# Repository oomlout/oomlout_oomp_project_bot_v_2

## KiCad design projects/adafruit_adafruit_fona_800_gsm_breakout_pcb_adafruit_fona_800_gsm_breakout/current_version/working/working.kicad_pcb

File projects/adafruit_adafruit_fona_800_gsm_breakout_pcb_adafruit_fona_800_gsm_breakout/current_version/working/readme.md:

# adafruit_fona_800_gsm_breakout_pcb
 
## summary 
* id: adafruit_adafruit_fona_800_gsm_breakout_pcb_adafruit_fona_800_gsm_breakout
* user: adafruit
* name: adafruit_fona_800_gsm_breakout_pcb
* board: adafruit_fona_800_gsm_breakout
* repo: https://github.com/adafruit/Adafruit-FONA-800-GSM-Breakout-PCB

* src_file_repo_sch: 
* src_file_repo_sch_link: https://github.com/adafruit/Adafruit-FONA-800-GSM-Breakout-PCB/tree/master/
* full details link: https://github.com/oomlout/oomlout_oomp_project_bot_v_2/tree/main/projects/adafruit_adafruit_fona_800_gsm_breakout_pcb_adafruit_fona_800_gsm_breakout/current_version/working  

## schematic  
  
[schematic (pdf)](working_schematic.pdf) 

## pcb  

[board (pdf)](working.pdf)  

## working_bom
| Id | Designator | Footprint | Quantity | Designation | Supplier and ref |  | None | 
| --- | --- | --- | --- | --- | --- | --- | --- | 
| 1 | U$34,U$33 | MOUNTINGHOLE_2.5_PLATED | 2 | MOUNTINGHOLE2.5 |  |  | [''] | 
| 2 | C1 | 0805-NO | 1 | 10ÂµF |  |  | [''] | 
| 3 | C17,C15 | RESPACK_4X0603 | 2 | 10pF |  |  | [''] | 
| 4 | D5,D6,D4,D3 | SOD-323 | 4 | 1N4148 |  |  | [''] | 
| 5 | CHRG0 | CHIPLED_0805_NOOUTLINE | 1 | ORANGE |  |  | [''] | 
| 6 | VBUS0,PWM0,ADC0 | 1X01-CLEANBIG | 3 |  |  |  | [''] | 
| 7 | PWRSTAT0,DONE0 | CHIPLED_0805_NOOUTLINE | 2 | GREEN |  |  | [''] | 
| 8 | D1 | SOD-123 | 1 | MMSZ5231BT1G |  |  | [''] | 
| 9 | R4,R2,R5 | 0805-NO | 3 | 1K |  |  | [''] | 
| 10 | SW1 | BTN_KMR2_4.6X2.8 | 1 | KMR2 |  |  | [''] | 
| 11 | C4,C6,C2 | 0805-NO | 3 | 33pF |  |  | [''] | 
| 12 | C9,C11 | 0805-NO | 2 | 10uF |  |  | [''] | 
| 13 | C3,C5,C10 | 0805-NO | 3 | 10pF |  |  | [''] | 
| 14 | FID1,FID3,FID2,FID5,FID4 | FIDUCIAL_1MM | 5 | FIDUCIAL" |  |  | [''] | 
| 15 | U1 | SIM800L | 1 | SIM800H/L |  |  | [''] | 
| 16 | R3 | 0805-NO | 1 | 2K |  |  | [''] | 
| 17 | C7 | C1210 | 1 | 100uF |  |  | [''] | 
| 18 | U2 | SOT23-5 | 1 | MCP73831T-2ACI/OT |  |  | [''] | 
| 19 | CN2 | JSTPH2 | 1 | JSTPH |  |  | [''] | 
| 20 | R1 | 0805-NO | 1 | 470 |  |  | [''] | 
| 21 | X4 | 4UCONN_18510 | 1 |  |  |  | [''] | 
| 22 | C14,C16 | RESPACK_4X0603 | 2 | 33pF |  |  | [''] | 
| 23 | Q1 | SC59-BEC | 1 | DTC143ZUAT106 |  |  | [''] | 
| 24 | U$10,U$36 | ADAFRUIT_5MM | 2 |  |  |  | [''] | 
| 25 | JP1 | 1X12-CB | 1 |  |  |  | [''] | 
| 26 | D2 | SOT363 | 1 | SMF05C |  |  | [''] | 
| 27 | TP1 | TP11R | 1 | TPTP11R |  |  | [''] | 
| 28 | X2 | 4UCONN_20329 | 1 | MicroB |  |  | [''] | 
| 29 | JP2 | 1X02_ROUND | 1 | MIC |  |  | [''] | 
| 30 | NETSTAT0 | CHIPLED_0805_NOOUTLINE | 1 | BLUE |  |  | [''] | 
| 31 | IC1 | TSSOP14 | 1 | 74VHCT125PW |  |  | [''] | 
| 32 | X1 | SMA_EDGELAUNCH_UFL | 1 |  |  |  | [''] | 
| 33 | JP3 | 1X02_ROUND | 1 | BUZZ |  |  | [''] | 
| 34 | U$26 | FONA_LOGO | 1 |  |  |  | [''] | 
| 35 | X6 | C707_10M006_512_2 | 1 | SIM_LOCKAMPHENOL |  |  | [''] | 

## bom_schematic
| Ref | Qnty | Value | Cmp name | Footprint | Description | Vendor | DNP | 
| --- | --- | --- | --- | --- | --- | --- | --- | 
| ADC0 | 1 | PINHD-1X1CB | PINHD-1X1CB | working:1X01-CLEANBIG |  |  |  | 
| C1 | 1 | 10ÂµF | CAP_CERAMIC0805-NOOUTLINE | working:0805-NO |  |  |  | 
| C2, C4, C6 | 3 | 33pF | CAP_CERAMIC0805-NOOUTLINE | working:0805-NO |  |  |  | 
| C3, C5, C10 | 3 | 10pF | CAP_CERAMIC0805-NOOUTLINE | working:0805-NO |  |  |  | 
| C7 | 1 | 100uF | C-USC1210 | working:C1210 |  |  |  | 
| C9, C11 | 2 | 10uF | CAP_CERAMIC0805-NOOUTLINE | working:0805-NO |  |  |  | 
| C14, C16 | 2 | 33pF | CAP_4PACK1206 | working:RESPACK_4X0603 |  |  |  | 
| C15, C17 | 2 | 10pF | CAP_4PACK1206 | working:RESPACK_4X0603 |  |  |  | 
| CHRG0 | 1 | ORANGE | LED0805_NOOUTLINE | working:CHIPLED_0805_NOOUTLINE |  |  |  | 
| CN2 | 1 | JSTPH | JST_2PIN | working:JSTPH2 |  |  |  | 
| D1 | 1 | MMSZ5231BT1G | DIODE-ZENERSOD123 | working:SOD-123 |  |  |  | 
| D2 | 1 | SMF05C | TVSARRAY_5LANE | working:SOT363 |  |  |  | 
| D3, D4, D5, D6 | 4 | 1N4148 | DIODESOD-323 | working:SOD-323 |  |  |  | 
| DONE0 | 1 | GREEN | LED0805_NOOUTLINE | working:CHIPLED_0805_NOOUTLINE |  |  |  | 
| FID1, FID2, FID3, FID4, FID5 | 5 | FIDUCIAL"" | FIDUCIAL{dblquote}{dblquote} | working:FIDUCIAL_1MM |  |  |  | 
| IC1 | 1 | 74125PW | 74125PW | working:TSSOP14 |  |  |  | 
| JP1 | 1 | PINHD-1X12-CB | PINHD-1X12-CB | working:1X12-CB |  |  |  | 
| JP2 | 1 | MIC | HEADER-1X2ROUND | working:1X02_ROUND |  |  |  | 
| JP3 | 1 | BUZZ | HEADER-1X2ROUND | working:1X02_ROUND |  |  |  | 
| NETSTAT0 | 1 | BLUE | LED0805_NOOUTLINE | working:CHIPLED_0805_NOOUTLINE |  |  |  | 
| PWM0 | 1 | PINHD-1X1CB | PINHD-1X1CB | working:1X01-CLEANBIG |  |  |  | 
| PWRSTAT0 | 1 | GREEN | LED0805_NOOUTLINE | working:CHIPLED_0805_NOOUTLINE |  |  |  | 
| Q1 | 1 | DTC143ZUAT106 | -NPN_DRIVER-SC59-BEC | working:SC59-BEC |  |  |  | 
| R1 | 1 | 470 | RESISTOR0805_NOOUTLINE | working:0805-NO |  |  |  | 
| R2, R4, R5 | 3 | 1K | RESISTOR0805_NOOUTLINE | working:0805-NO |  |  |  | 
| R3 | 1 | 2K | RESISTOR0805_NOOUTLINE | working:0805-NO |  |  |  | 
| SW1 | 1 | KMR2 | SWITCH_TACT_SMT4.6X2.8 | working:BTN_KMR2_4.6X2.8 |  |  |  | 
| TP1 | 1 | TPTP11R | TPTP11R | working:TP11R |  |  |  | 
| U1 | 1 | SIM800H/L | GSM_SIM800L | working:SIM800L |  |  |  | 
| U2 | 1 | MCP73831T-2ACI/OT | MCP73831/2 | working:SOT23-5 |  |  |  | 
| U$33, U$34 | 2 | MOUNTINGHOLE2.5 | MOUNTINGHOLE2.5 | working:MOUNTINGHOLE_2.5_PLATED |  |  |  | 
| VBUS0 | 1 | PINHD-1X1CB | PINHD-1X1CB | working:1X01-CLEANBIG |  |  |  | 
| X1 | 1 | SMACONNECTOR_EDGE_UFL | SMACONNECTOR_EDGE_UFL | working:SMA_EDGELAUNCH_UFL |  |  |  | 
| X2 | 1 | MicroB | USBMICRO_20329 | working:4UCONN_20329 |  |  |  | 
| X4 | 1 | AUDIO_3.5MMJACK_4POL | AUDIO_3.5MMJACK_4POL | working:4UCONN_18510 |  |  |  | 
| X6 | 1 | SIM_LOCKAMPHENOL | SIM_LOCKAMPHENOL | working:C707_10M006_512_2 |  |  |  | 

## mounting_holes
| x | y | package | value | ref | size | 
| --- | --- | --- | --- | --- | --- | 
| 26.67 | 0.0 | MOUNTINGHOLE_2.5_PLATED | MOUNTINGHOLE2.5 | U$33 | m3 | 
| 0.0 | 0.0 | MOUNTINGHOLE_2.5_PLATED | MOUNTINGHOLE2.5 | U$34 | m3 |

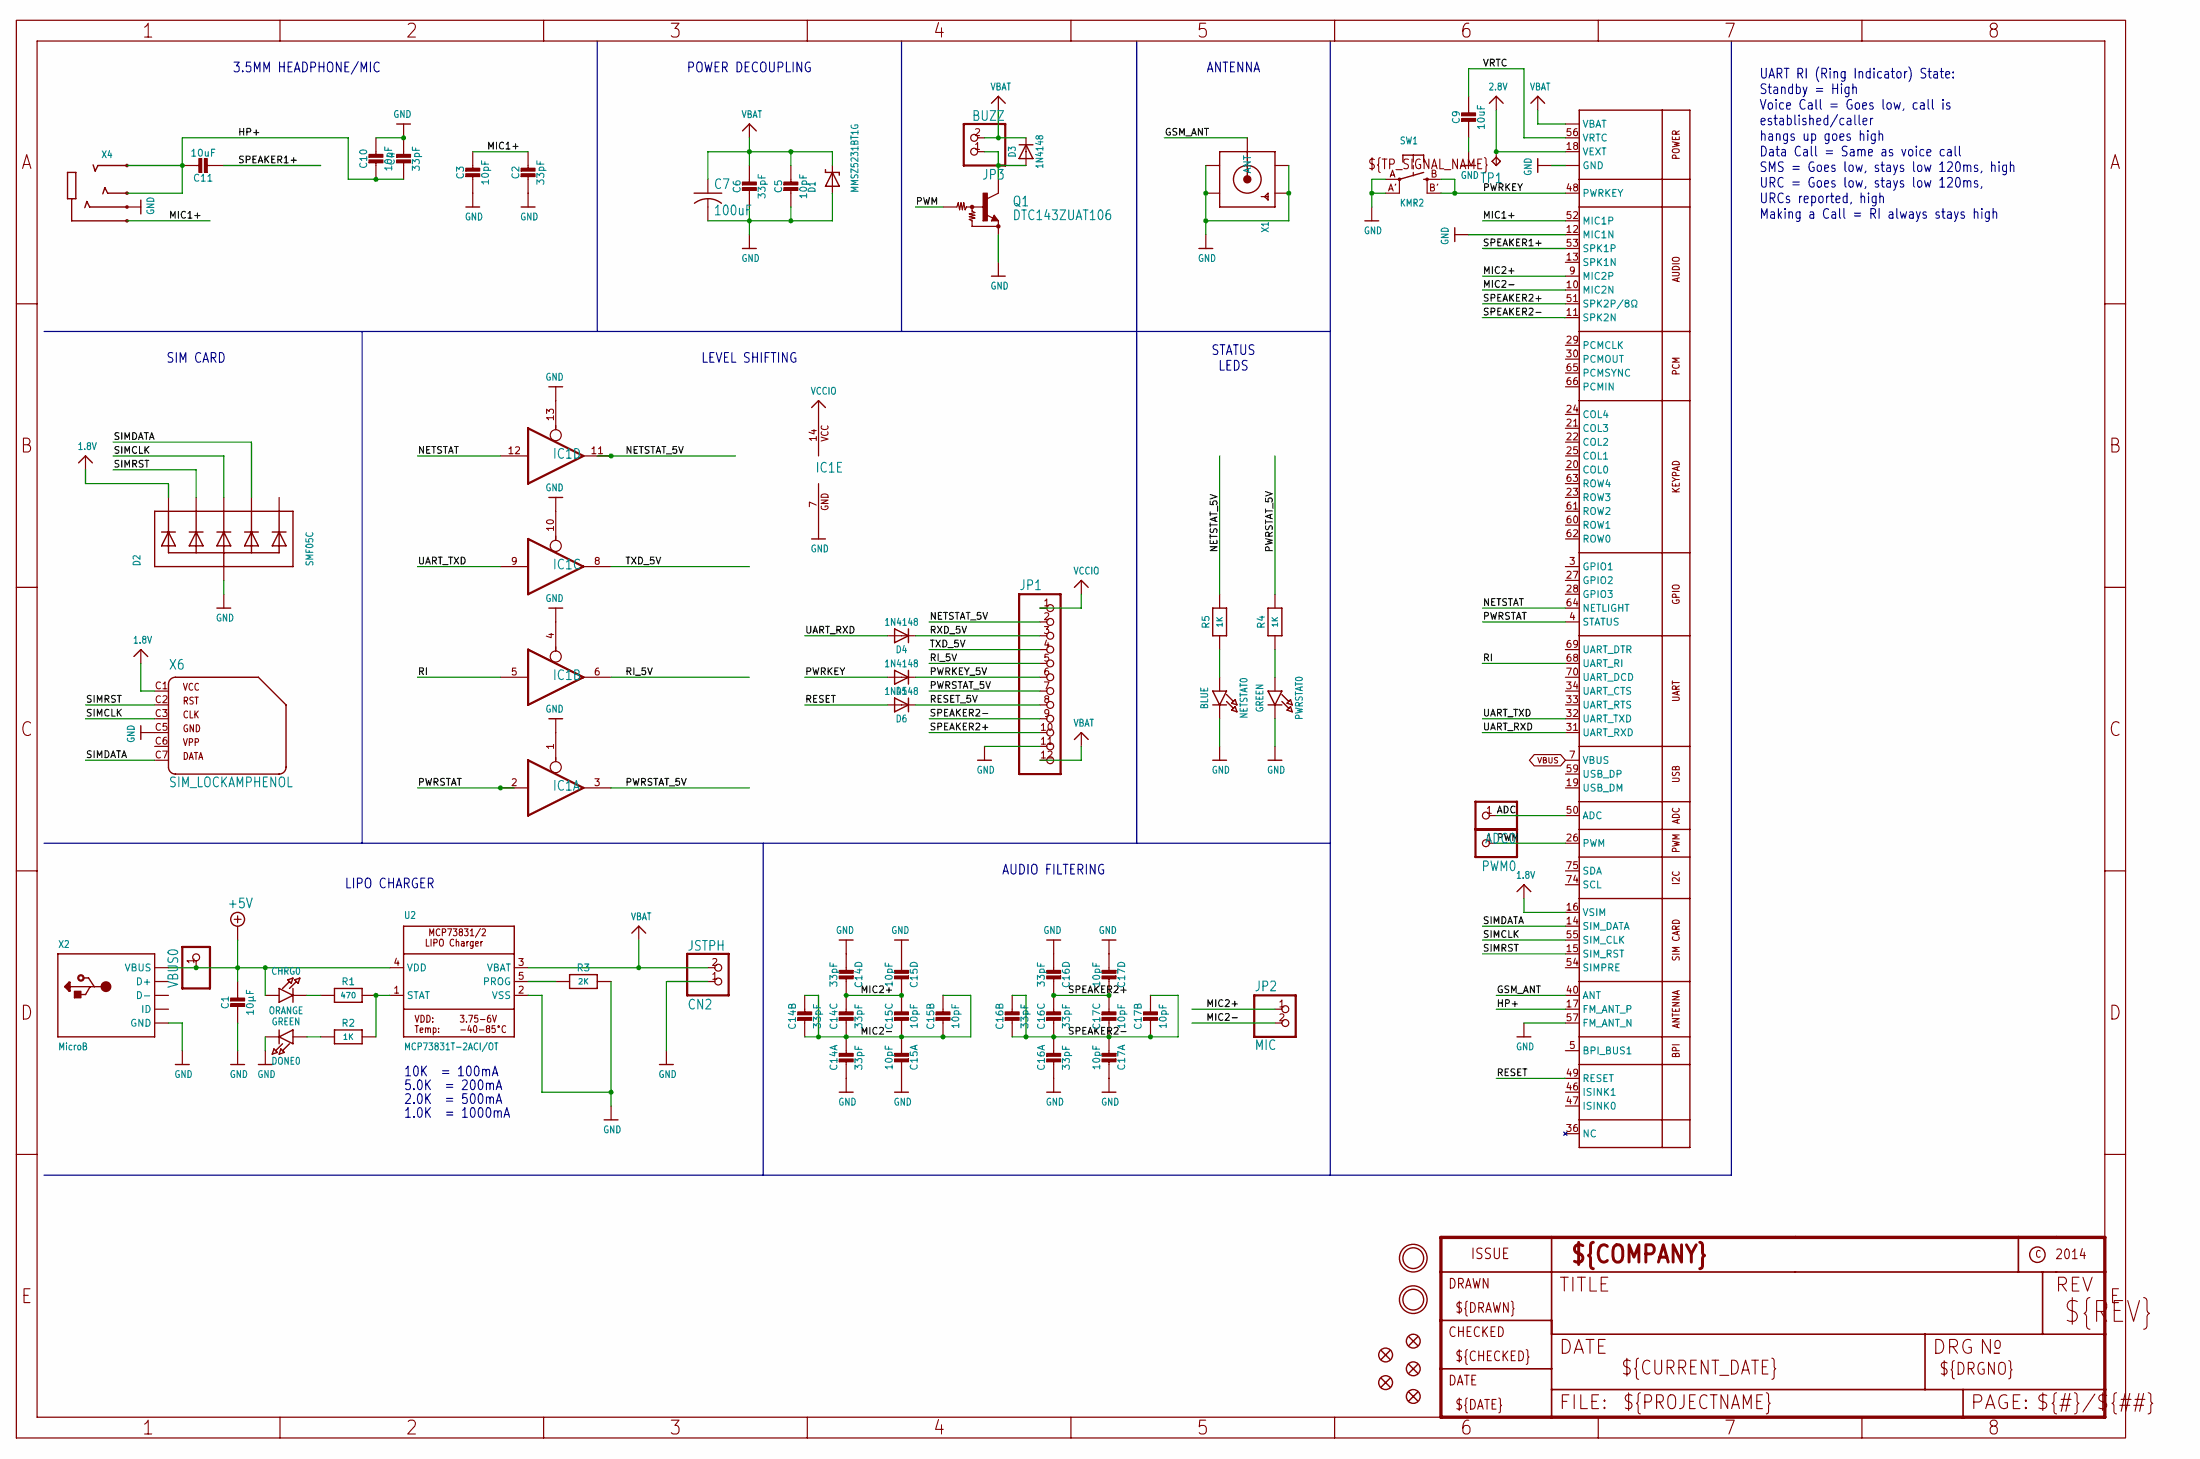
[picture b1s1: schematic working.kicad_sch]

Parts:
ADC0: PINHD-1X1CB; 1X01-CLEANBIG
C1: 10µF; 0805-NO
C2, C4, C6: 33pF; 0805-NO
C3, C5, C10: 10pF; 0805-NO
C7: 100uF; C1210
C9, C11: 10uF; 0805-NO
C14, C16: 33pF; RESPACK_4X0603
C15, C17: 10pF; RESPACK_4X0603
CHRG0: ORANGE; CHIPLED_0805_NOOUTLINE
CN2: JSTPH; JSTPH2
D1: MMSZ5231BT1G; SOD-123
D2: SMF05C; SOT363
D3, D4, D5, D6: 1N4148; SOD-323
DONE0: GREEN; CHIPLED_0805_NOOUTLINE
FID1, FID2, FID3, FID4, FID5: FIDUCIAL""; FIDUCIAL_1MM
IC1: 74125PW; TSSOP14
JP1: PINHD-1X12-CB; 1X12-CB
JP2: MIC; 1X02_ROUND
JP3: BUZZ; 1X02_ROUND
NETSTAT0: BLUE; CHIPLED_0805_NOOUTLINE
PWM0: PINHD-1X1CB; 1X01-CLEANBIG
PWRSTAT0: GREEN; CHIPLED_0805_NOOUTLINE
Q1: DTC143ZUAT106; SC59-BEC
R1: 470; 0805-NO
R2, R4, R5: 1K; 0805-NO
R3: 2K; 0805-NO
SW1: KMR2; BTN_KMR2_4.6X2.8
TP1: TPTP11R; TP11R
U1: SIM800H/L; SIM800L
U2: MCP73831T-2ACI/OT; SOT23-5
U$33, U$34: MOUNTINGHOLE2.5; MOUNTINGHOLE_2.5_PLATED
VBUS0: PINHD-1X1CB; 1X01-CLEANBIG
X1: SMACONNECTOR_EDGE_UFL; SMA_EDGELAUNCH_UFL
X2: MicroB; 4UCONN_20329
X4: AUDIO_3.5MMJACK_4POL; 4UCONN_18510
X6: SIM_LOCKAMPHENOL; C707_10M006_512_2

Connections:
1.8V: D2.1 (C1), U1.16 (VSIM), X6.C1 (1)
2.8V: TP1.TP, U1.18 (VEXT)
+5V: C1.1, CHRG0.A, U2.4 (VDD), VBUS0.1, X2.VBUS
ADC: ADC0.1, U1.50 (ADC)
GND: C1.2, C2.2, C3.2, C4.1, C5.2, C6.2, C7.2, C9.2, C10.1, C14.5 (2), C14.8 (2), C15.4 (1), C15.8 (2), C16.5 (2), C16.8 (2), C17.4 (1), C17.8 (2), CN2.1, D1.A, D2.2 (A), DONE0.C, IC1.1 (OE), IC1.4 (OE), IC1.7 (GND), IC1.10 (OE), IC1.13 (OE), JP1.11, NETSTAT0.C, PWRSTAT0.C, Q1.E, R3.2, SW1.A, SW1.A' (P1), U1.2 (GND), U1.6 (GND), U1.8 (GND), U1.12 (MIC1N), U1.35 (GND), U1.37 (GND), U1.38 (GND), U1.39 (GND), U1.41 (GND), U1.43 (GND), U1.44 (GND), U1.45 (GND), U1.57 (FM_ANT_N), U1.58 (GND), U1.67 (GND), U1.71 (GND), U1.72 (GND), U1.73 (GND), U1.76 (GND), U1.77 (GND), U1.78 (GND), U1.79 (GND), U1.80 (GND), U1.81 (GND), U1.82 (GND), U1.83 (GND), U1.84 (GND), U1.85 (GND), U1.86 (GND), U1.87 (GND), U1.88 (GND), U2.2 (VSS), X1.GND@1 (GND1), X1.GND@2 (GND2), X1.GND@3 (GND3), X1.GND@4 (GND4), X2.BASE@1 (GND), X2.BASE@2 (GND), X2.GND, X2.SPRT@1 (GND), X2.SPRT@2 (GND), X2.SPRT@3 (GND), X2.SPRT@4 (GND), X4.4-INNER_SLEEVE (RING1), X6.C5 (4)
GSM_ANT: U1.40 (ANT), X1.P (ANT)
HP+: C4.2, C10.2, C11.1, U1.17 (FM_ANT_P), X4.2-TIP (RING3), X4.3-OUTER_SLEEVE (RING2)
MIC1+: C2.1, C3.1, U1.52 (MIC1P), X4.1-GND (TIP)
MIC2+: C14.1, C14.2 (1), C15.1, C15.2 (1), JP2.1, U1.9 (MIC2P)
MIC2-: C14.3 (1), C14.4 (1), C14.6 (2), C14.7 (2), C15.3 (1), C15.5 (2), C15.6 (2), C15.7 (2), JP2.2, U1.10 (MIC2N)
unnamed: CHRG0.C, R1.1
unnamed: R1.2, R2.2, U2.1 (STAT)
unnamed: PWRSTAT0.A, R4.1
unnamed: R3.1, U2.5 (PROG)
unnamed: DONE0.A, R2.1
unnamed: NETSTAT0.A, R5.1
unnamed: D3.A, JP3.1, Q1.C
NETSTAT: IC1.12 (I), U1.64 (NETLIGHT)
NETSTAT_5V: IC1.11 (O), JP1.2, R5.2
PWM: PWM0.1, Q1.B, U1.26 (PWM)
PWRKEY: D5.A, SW1.B (S), SW1.B' (S1), U1.48 (PWRKEY)
PWRKEY_5V: D5.C, JP1.6
PWRSTAT: IC1.2 (I), U1.4 (STATUS)
PWRSTAT_5V: IC1.3 (O), JP1.7, R4.2
RESET: D6.A, U1.49 (RESET)
RESET_5V: D6.C, JP1.8
RI: IC1.5 (I), U1.68 (UART_RI)
RI_5V: IC1.6 (O), JP1.5
RXD_5V: D4.C, JP1.3
SIMCLK: D2.4 (C3), U1.55 (SIM_CLK), X6.C3 (3)
SIMDATA: D2.5 (C4), U1.14 (SIM_DATA), X6.C7 (6)
SIMRST: D2.3 (C2), U1.15 (SIM_RST), X6.C2 (2)
SPEAKER1+: C11.2, U1.53 (SPK1P)
SPEAKER2+: C16.1, C16.2 (1), C17.1, C17.2 (1), JP1.10, U1.51 (SPK2P/8Ω)
SPEAKER2-: C16.3 (1), C16.4 (1), C16.6 (2), C16.7 (2), C17.3 (1), C17.5 (2), C17.6 (2), C17.7 (2), JP1.9, U1.11 (SPK2N)
TXD_5V: IC1.8 (O), JP1.4
UART_RXD: D4.A, U1.31 (UART_RXD)
UART_TXD: IC1.9 (I), U1.32 (UART_TXD)
VBAT: C5.1, C6.1, C7.1, CN2.2, D1.C, D3.C, JP1.12, JP3.2, U1.1 (VBAT), U1.42 (VBAT), U2.3 (VBAT)
VBUS: U1.7 (VBUS)
VCCIO: IC1.14 (VCC), JP1.1
VRTC: C9.1, U1.56 (VRTC)

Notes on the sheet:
POWER DECOUPLING
5.0K = 200mA
1.0K = 1000mA
ANTENNA
2.0K = 500mA
UART RI (Ring Indicator) State: Standby = High Voice Call = Goes low, call is established/caller hangs up goes high Data Call = Same as voice call SMS = Goes low, stays low 120ms, high URC = Goes low, stays low 120ms, URCs reported, high Making a Call = RI always stays high
AUDIO FILTERING
3.5MM HEADPHONE/MIC
STATUS LEDS
SIM CARD
10K = 100mA
LEVEL SHIFTING
LIPO CHARGER

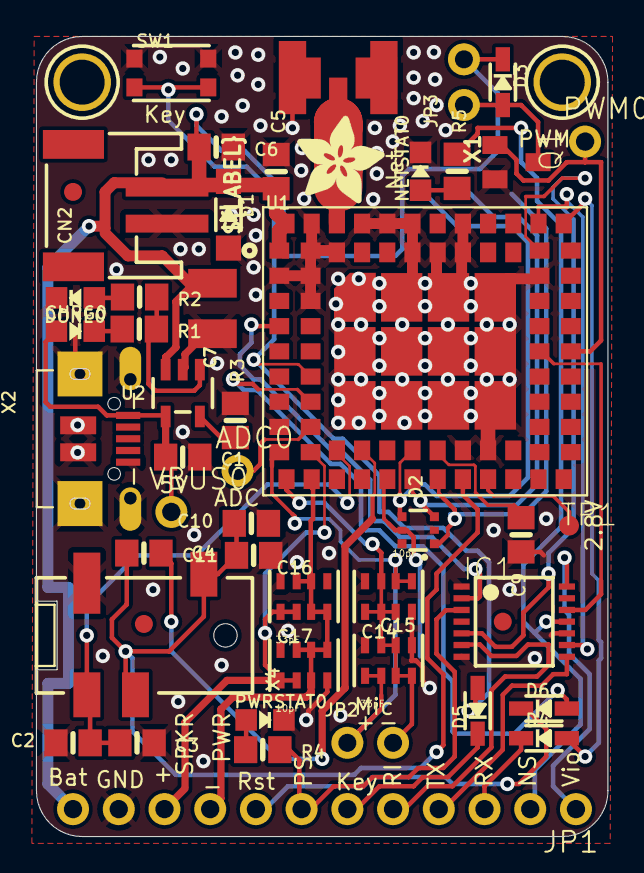
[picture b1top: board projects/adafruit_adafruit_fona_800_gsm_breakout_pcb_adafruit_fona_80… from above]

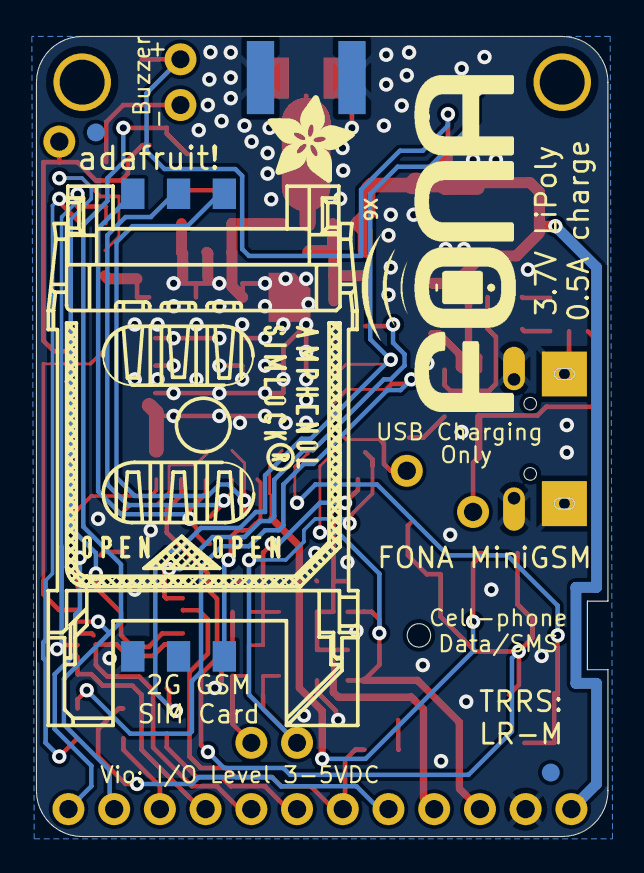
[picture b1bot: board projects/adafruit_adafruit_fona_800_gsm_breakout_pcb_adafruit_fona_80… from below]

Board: 2 copper layers, 31.8 x 44.5 mm, 56 parts (5 on the bottom side), 41 nets.

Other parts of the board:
U$10, U$36: ADAFRUIT_5MM
U$26: FONA_LOGO

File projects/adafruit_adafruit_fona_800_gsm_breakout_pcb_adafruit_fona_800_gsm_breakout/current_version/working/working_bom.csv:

"Id";"Designator";"Footprint";"Quantity";"Designation";"Supplier and ref";
1;"U$34,U$33";"MOUNTINGHOLE_2.5_PLATED";2;"MOUNTINGHOLE2.5";;;
2;"C1";"0805-NO";1;"10µF";;;
3;"C17,C15";"RESPACK_4X0603";2;"10pF";;;
4;"D5,D6,D4,D3";"SOD-323";4;"1N4148";;;
5;"CHRG0";"CHIPLED_0805_NOOUTLINE";1;"ORANGE";;;
6;"VBUS0,PWM0,ADC0";"1X01-CLEANBIG";3;"";;;
7;"PWRSTAT0,DONE0";"CHIPLED_0805_NOOUTLINE";2;"GREEN";;;
8;"D1";"SOD-123";1;"MMSZ5231BT1G";;;
9;"R4,R2,R5";"0805-NO";3;"1K";;;
10;"SW1";"BTN_KMR2_4.6X2.8";1;"KMR2";;;
11;"C4,C6,C2";"0805-NO";3;"33pF";;;
12;"C9,C11";"0805-NO";2;"10uF";;;
13;"C3,C5,C10";"0805-NO";3;"10pF";;;
14;"FID1,FID3,FID2,FID5,FID4";"FIDUCIAL_1MM";5;"FIDUCIAL""";;;
15;"U1";"SIM800L";1;"SIM800H/L";;;
16;"R3";"0805-NO";1;"2K";;;
17;"C7";"C1210";1;"100uF";;;
18;"U2";"SOT23-5";1;"MCP73831T-2ACI/OT";;;
19;"CN2";"JSTPH2";1;"JSTPH";;;
20;"R1";"0805-NO";1;"470";;;
21;"X4";"4UCONN_18510";1;"";;;
22;"C14,C16";"RESPACK_4X0603";2;"33pF";;;
23;"Q1";"SC59-BEC";1;"DTC143ZUAT106";;;
24;"U$10,U$36";"ADAFRUIT_5MM";2;"";;;
25;"JP1";"1X12-CB";1;"";;;
26;"D2";"SOT363";1;"SMF05C";;;
27;"TP1";"TP11R";1;"TPTP11R";;;
28;"X2";"4UCONN_20329";1;"MicroB";;;
29;"JP2";"1X02_ROUND";1;"MIC";;;
30;"NETSTAT0";"CHIPLED_0805_NOOUTLINE";1;"BLUE";;;
31;"IC1";"TSSOP14";1;"74VHCT125PW";;;
32;"X1";"SMA_EDGELAUNCH_UFL";1;"";;;
33;"JP3";"1X02_ROUND";1;"BUZZ";;;
34;"U$26";"FONA_LOGO";1;"";;;
35;"X6";"C707_10M006_512_2";1;"SIM_LOCKAMPHENOL";;;

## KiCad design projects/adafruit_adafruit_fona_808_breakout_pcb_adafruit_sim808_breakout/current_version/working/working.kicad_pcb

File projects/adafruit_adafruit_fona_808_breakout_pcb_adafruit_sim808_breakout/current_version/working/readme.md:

# adafruit_fona_808_breakout_pcb
 
## summary 
* id: adafruit_adafruit_fona_808_breakout_pcb_adafruit_sim808_breakout
* user: adafruit
* name: adafruit_fona_808_breakout_pcb
* board: adafruit_sim808_breakout
* repo: https://github.com/adafruit/Adafruit-FONA-808-Breakout-PCB

* src_file_repo_sch: 
* src_file_repo_sch_link: https://github.com/adafruit/Adafruit-FONA-808-Breakout-PCB/tree/master/
* full details link: https://github.com/oomlout/oomlout_oomp_project_bot_v_2/tree/main/projects/adafruit_adafruit_fona_808_breakout_pcb_adafruit_sim808_breakout/current_version/working  

## schematic  
  
[schematic (pdf)](working_schematic.pdf) 

## pcb  

[board (pdf)](working.pdf)  

## working_bom
| Id | Designator | Footprint | Quantity | Designation | Supplier and ref |  | None | 
| --- | --- | --- | --- | --- | --- | --- | --- | 
| 1 | JP10 | 1X16_ROUND | 1 |  |  |  | [''] | 
| 2 | U$33,U$34 | MOUNTINGHOLE_2.5_PLATED | 2 | MOUNTINGHOLE2.5 |  |  | [''] | 
| 3 | D5,D6,D4,D3,D7 | SOD-323 | 5 | 1N4148 |  |  | [''] | 
| 4 | X4 | 4UCONN_18510 | 1 | 4UCONN_18510 |  |  | [''] | 
| 5 | C14,C16 | RESPACK_4X0603 | 2 | 33pF |  |  | [''] | 
| 6 | R6 | 0805-NO | 1 | 10K |  |  | [''] | 
| 7 | C1 | 0805-NO | 1 | 10ÂµF |  |  | [''] | 
| 8 | U2 | SOT23-5 | 1 | MCP73831T-2ACI/OT |  |  | [''] | 
| 9 | FID3,FID1,FID2,FID5,FID4 | FIDUCIAL_1MM | 5 | FIDUCIAL" |  |  | [''] | 
| 10 | ADC1,PWM0 | 1X01-CLEANBIG | 2 |  |  |  | [''] | 
| 11 | C6 | 0805-NO | 1 | 33pF |  |  | [''] | 
| 12 | CHRG0 | CHIPLED_0805_NOOUTLINE | 1 | ORANGE |  |  | [''] | 
| 13 | PWRSTAT0 | CHIPLED_0805_NOOUTLINE | 1 | BLUE |  |  | [''] | 
| 14 | R2,R5,R4 | 0805-NO | 3 | 1K |  |  | [''] | 
| 15 | X1 | SMA_EDGELAUNCH_UFL | 1 | uFL |  |  | [''] | 
| 16 | C9,C11 | 0805-NO | 2 | 10uF |  |  | [''] | 
| 17 | C5 | 0805-NO | 1 | 10pF |  |  | [''] | 
| 18 | C17,C15 | RESPACK_4X0603 | 2 | 10pF |  |  | [''] | 
| 19 | U3 | SIM900_SMT | 1 | SIM808 |  |  | [''] | 
| 20 | JP3 | 1X02_ROUND | 1 | BUZZ |  |  | [''] | 
| 21 | R1 | 0805-NO | 1 | 470 |  |  | [''] | 
| 22 | U$21 | ADAFRUIT_2.5MM | 1 |  |  |  | [''] | 
| 23 | Q1 | SC59-BEC | 1 | DTC143ZUAT106 |  |  | [''] | 
| 24 | D2 | SOT363 | 1 | SMF05C |  |  | [''] | 
| 25 | DONE0 | CHIPLED_0805_NOOUTLINE | 1 | GREEN |  |  | [''] | 
| 26 | X2 | 4UCONN_20329 | 1 | MicroB |  |  | [''] | 
| 27 | R3 | 0805-NO | 1 | 2K |  |  | [''] | 
| 28 | NETSTAT0 | CHIPLED_0805_NOOUTLINE | 1 | RED |  |  | [''] | 
| 29 | C7 | C1210 | 1 | 100uF |  |  | [''] | 
| 30 | TP1 | TP11R | 1 | TPTP11R |  |  | [''] | 
| 31 | SW1 | BTN_KMR2_4.6X2.8 | 1 | KMR2 |  |  | [''] | 
| 32 | CN2 | JSTPH2 | 1 | JSTPH |  |  | [''] | 
| 33 | IC1 | TSSOP14 | 1 | 74VHCT125PW |  |  | [''] | 
| 34 | X3 | U.FL | 1 | uFL |  |  | [''] | 
| 35 | D1 | SOD-123 | 1 | MMSZ5231BT1G |  |  | [''] | 
| 36 | X6 | C707_10M006_512_2 | 1 | SIM_LOCKAMPHENOL |  |  | [''] | 
| 37 | U$36 | ADAFRUIT_5MM | 1 |  |  |  | [''] | 
| 38 | U$25 | PCBFEAT-REV-040 | 1 |  |  |  | [''] | 
| 39 | U$26 | FONA_LOGO | 1 |  |  |  | [''] | 

## bom_schematic
| Ref | Qnty | Value | Cmp name | Footprint | Description | Vendor | DNP | 
| --- | --- | --- | --- | --- | --- | --- | --- | 
| ADC1 | 1 | PINHD-1X1CB | PINHD-1X1CB | working:1X01-CLEANBIG |  |  |  | 
| C1 | 1 | 10ÂµF | CAP_CERAMIC0805-NOOUTLINE | working:0805-NO |  |  |  | 
| C5 | 1 | 10pF | CAP_CERAMIC0805-NOOUTLINE | working:0805-NO |  |  |  | 
| C6 | 1 | 33pF | CAP_CERAMIC0805-NOOUTLINE | working:0805-NO |  |  |  | 
| C7 | 1 | 100uF | C-USC1210 | working:C1210 |  |  |  | 
| C9, C11 | 2 | 10uF | CAP_CERAMIC0805-NOOUTLINE | working:0805-NO |  |  |  | 
| C14, C16 | 2 | 33pF | CAP_4PACK1206 | working:RESPACK_4X0603 |  |  |  | 
| C15, C17 | 2 | 10pF | CAP_4PACK1206 | working:RESPACK_4X0603 |  |  |  | 
| CHRG0 | 1 | ORANGE | LED0805_NOOUTLINE | working:CHIPLED_0805_NOOUTLINE |  |  |  | 
| CN2 | 1 | JSTPH | JST_2PIN | working:JSTPH2 |  |  |  | 
| D1 | 1 | MMSZ5231BT1G | DIODE-ZENERSOD123 | working:SOD-123 |  |  |  | 
| D2 | 1 | SMF05C | TVSARRAY_5LANE | working:SOT363 |  |  |  | 
| D3, D4, D5, D6, D7 | 5 | 1N4148 | DIODESOD-323 | working:SOD-323 |  |  |  | 
| DONE0 | 1 | GREEN | LED0805_NOOUTLINE | working:CHIPLED_0805_NOOUTLINE |  |  |  | 
| FID1, FID2, FID3, FID4, FID5 | 5 | FIDUCIAL"" | FIDUCIAL{dblquote}{dblquote} | working:FIDUCIAL_1MM |  |  |  | 
| IC1 | 1 | 74125PW | 74125PW | working:TSSOP14 |  |  |  | 
| JP3 | 1 | BUZZ | HEADER-1X2ROUND | working:1X02_ROUND |  |  |  | 
| JP10 | 1 | HEADER-1X16ROUND | HEADER-1X16ROUND | working:1X16_ROUND |  |  |  | 
| NETSTAT0 | 1 | RED | LED0805_NOOUTLINE | working:CHIPLED_0805_NOOUTLINE |  |  |  | 
| PWM0 | 1 | PINHD-1X1CB | PINHD-1X1CB | working:1X01-CLEANBIG |  |  |  | 
| PWRSTAT0 | 1 | BLUE | LED0805_NOOUTLINE | working:CHIPLED_0805_NOOUTLINE |  |  |  | 
| Q1 | 1 | DTC143ZUAT106 | -NPN_DRIVER-SC59-BEC | working:SC59-BEC |  |  |  | 
| R1 | 1 | 470 | RESISTOR0805_NOOUTLINE | working:0805-NO |  |  |  | 
| R2, R4, R5 | 3 | 1K | RESISTOR0805_NOOUTLINE | working:0805-NO |  |  |  | 
| R3 | 1 | 2K | RESISTOR0805_NOOUTLINE | working:0805-NO |  |  |  | 
| R6 | 1 | 10K | RESISTOR0805_NOOUTLINE | working:0805-NO |  |  |  | 
| SW1 | 1 | KMR2 | SWITCH_TACT_SMT4.6X2.8 | working:BTN_KMR2_4.6X2.8 |  |  |  | 
| TP1 | 1 | TPTP11R | TPTP11R | working:TP11R |  |  |  | 
| U2 | 1 | MCP73831T-2ACI/OT | MCP73831/2 | working:SOT23-5 |  |  |  | 
| U3 | 1 | SIM808 | GSM_SIM808_LITERAL | working:SIM900_SMT |  |  |  | 
| U$33, U$34 | 2 | MOUNTINGHOLE2.5 | MOUNTINGHOLE2.5 | working:MOUNTINGHOLE_2.5_PLATED |  |  |  | 
| X1 | 1 | uFL | SMACONNECTOR_EDGE_UFL | working:SMA_EDGELAUNCH_UFL |  |  |  | 
| X2 | 1 | MicroB | USBMICRO_20329 | working:4UCONN_20329 |  |  |  | 
| X3 | 1 | uFL | ANTENNA_U.FL | working:U.FL |  |  |  | 
| X4 | 1 | 4UCONN_18510 | AUDIO_3.5MMJACK_4POL | working:4UCONN_18510 |  |  |  | 
| X6 | 1 | SIM_LOCKAMPHENOL | SIM_LOCKAMPHENOL | working:C707_10M006_512_2 |  |  |  | 

## mounting_holes
| x | y | package | value | ref | size | 
| --- | --- | --- | --- | --- | --- | 
| 35.56 | 0.0 | MOUNTINGHOLE_2.5_PLATED | MOUNTINGHOLE2.5 | U$33 | m3 | 
| 0.0 | 0.0 | MOUNTINGHOLE_2.5_PLATED | MOUNTINGHOLE2.5 | U$34 | m3 |

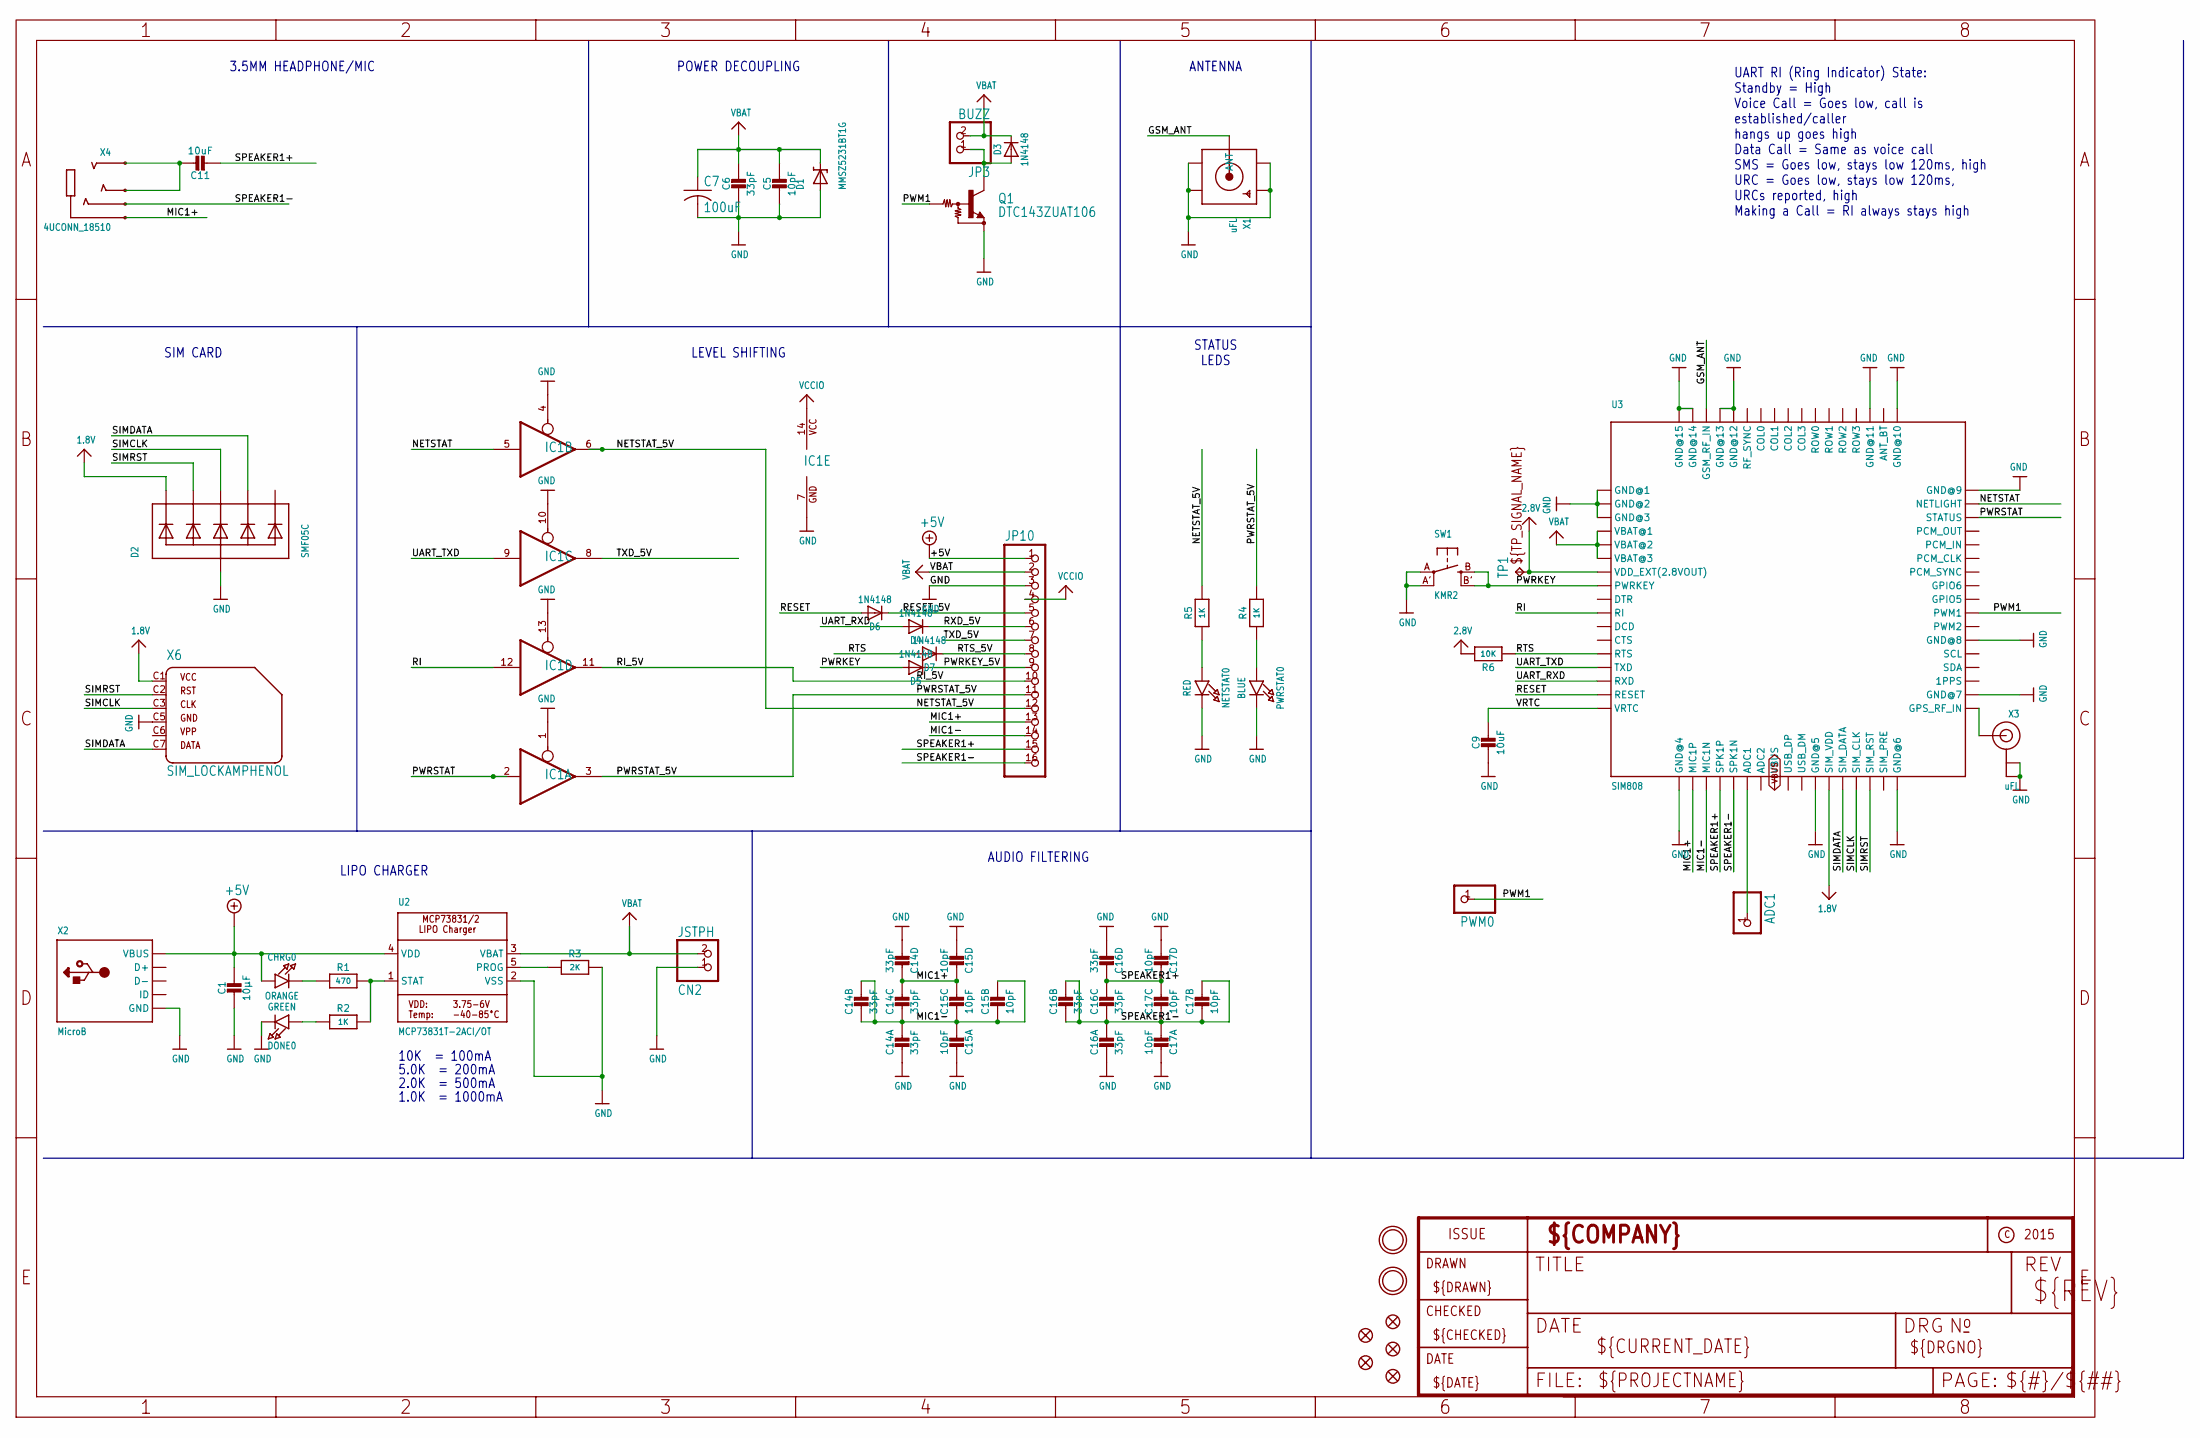
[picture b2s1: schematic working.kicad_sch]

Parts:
ADC1: PINHD-1X1CB; 1X01-CLEANBIG
C1: 10µF; 0805-NO
C5: 10pF; 0805-NO
C6: 33pF; 0805-NO
C7: 100uF; C1210
C9, C11: 10uF; 0805-NO
C14, C16: 33pF; RESPACK_4X0603
C15, C17: 10pF; RESPACK_4X0603
CHRG0: ORANGE; CHIPLED_0805_NOOUTLINE
CN2: JSTPH; JSTPH2
D1: MMSZ5231BT1G; SOD-123
D2: SMF05C; SOT363
D3, D4, D5, D6, D7: 1N4148; SOD-323
DONE0: GREEN; CHIPLED_0805_NOOUTLINE
FID1, FID2, FID3, FID4, FID5: FIDUCIAL""; FIDUCIAL_1MM
IC1: 74125PW; TSSOP14
JP3: BUZZ; 1X02_ROUND
JP10: HEADER-1X16ROUND; 1X16_ROUND
NETSTAT0: RED; CHIPLED_0805_NOOUTLINE
PWM0: PINHD-1X1CB; 1X01-CLEANBIG
PWRSTAT0: BLUE; CHIPLED_0805_NOOUTLINE
Q1: DTC143ZUAT106; SC59-BEC
R1: 470; 0805-NO
R2, R4, R5: 1K; 0805-NO
R3: 2K; 0805-NO
R6: 10K; 0805-NO
SW1: KMR2; BTN_KMR2_4.6X2.8
TP1: TPTP11R; TP11R
U2: MCP73831T-2ACI/OT; SOT23-5
U3: SIM808; SIM900_SMT
U$33, U$34: MOUNTINGHOLE2.5; MOUNTINGHOLE_2.5_PLATED
X1: uFL; SMA_EDGELAUNCH_UFL
X2: MicroB; 4UCONN_20329
X3: uFL; U.FL
X4: 4UCONN_18510
X6: SIM_LOCKAMPHENOL; C707_10M006_512_2

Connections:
1.8V: D2.1 (C1), U3.P$29 (SIM_VDD), X6.C1 (1)
2.8V: R6.2, TP1.TP, U3.P$7 (VDD_EXT(2.8VOUT))
+5V: C1.1, CHRG0.A, JP10.1, U2.4 (VDD), X2.VBUS
GND: C1.2, C5.2, C6.2, C7.2, C9.2, C14.5 (2), C14.8 (2), C15.4 (1), C15.8 (2), C16.5 (2), C16.8 (2), C17.4 (1), C17.8 (2), CN2.1, D1.A, D2.2 (A), DONE0.C, IC1.1 (OE), IC1.4 (OE), IC1.7 (GND), IC1.10 (OE), IC1.13 (OE), JP10.3, NETSTAT0.C, PWRSTAT0.C, Q1.E, R3.2, SW1.A, SW1.A' (P1), U2.2 (VSS), U3.P$1 (GND@1), U3.P$2 (GND@2), U3.P$3 (GND@3), U3.P$18 (GND@4), U3.P$28 (GND@5), U3.P$34 (GND@6), U3.P$36 (GND@7), U3.P$40 (GND@8), U3.P$51 (GND@9), U3.P$52 (GND@10), U3.P$54 (GND@11), U3.P$64 (GND@12), U3.P$65 (GND@13), U3.P$67 (GND@14), U3.P$68 (GND@15), X1.GND@1 (GND1), X1.GND@2 (GND2), X1.GND@3 (GND3), X1.GND@4 (GND4), X2.BASE@1 (GND), X2.BASE@2 (GND), X2.GND, X2.SPRT@1 (GND), X2.SPRT@2 (GND), X2.SPRT@3 (GND), X2.SPRT@4 (GND), X3.1 (GND@0), X3.2 (GND@1), X6.C5 (4)
GSM_ANT: U3.P$66 (GSM_RF_IN), X1.P (ANT)
HP+: C11.1, X4.2-TIP (RING3), X4.3-OUTER_SLEEVE (RING2)
MIC1+: C14.1, C14.2 (1), C15.1, C15.2 (1), JP10.13, U3.P$19 (MIC1P), X4.1-GND (TIP)
MIC1-: C14.3 (1), C14.4 (1), C14.6 (2), C14.7 (2), C15.3 (1), C15.5 (2), C15.6 (2), C15.7 (2), JP10.14, U3.P$20 (MIC1N)
unnamed: CHRG0.C, R1.1
unnamed: R1.2, R2.2, U2.1 (STAT)
unnamed: U3.P$35 (GPS_RF_IN), X3.3 (SIGNAL)
unnamed: PWRSTAT0.A, R4.1
unnamed: R3.1, U2.5 (PROG)
unnamed: DONE0.A, R2.1
unnamed: ADC1.1, U3.P$23 (ADC1)
unnamed: NETSTAT0.A, R5.1
unnamed: D3.A, JP3.1, Q1.C
NETSTAT: IC1.5 (I), U3.P$50 (NETLIGHT)
NETSTAT_5V: IC1.6 (O), JP10.12, R5.2
PWM1: PWM0.1, Q1.B, U3.P$42 (PWM1)
PWRKEY: D5.A, SW1.B (S), SW1.B' (S1), U3.P$8 (PWRKEY)
PWRKEY_5V: D5.C, JP10.9
PWRSTAT: IC1.2 (I), U3.P$49 (STATUS)
PWRSTAT_5V: IC1.3 (O), JP10.11, R4.2
RESET: D6.A, U3.P$16 (RESET)
RESET_5V: D6.C, JP10.5
RI: IC1.12 (I), U3.P$10 (RI)
RI_5V: IC1.11 (O), JP10.10
RTS: D7.A, R6.1, U3.P$13 (RTS)
RTS_5V: D7.C, JP10.8
RXD_5V: D4.C, JP10.6
SIMCLK: D2.4 (C3), U3.P$31 (SIM_CLK), X6.C3 (3)
SIMDATA: D2.5 (C4), U3.P$30 (SIM_DATA), X6.C7 (6)
SIMRST: D2.3 (C2), U3.P$32 (SIM_RST), X6.C2 (2)
SPEAKER1+: C11.2, C16.1, C16.2 (1), C17.1, C17.2 (1), JP10.15, U3.P$21 (SPK1P)
SPEAKER1-: C16.3 (1), C16.4 (1), C16.6 (2), C16.7 (2), C17.3 (1), C17.5 (2), C17.6 (2), C17.7 (2), JP10.16, U3.P$22 (SPK1N), X4.4-INNER_SLEEVE (RING1)
TXD_5V: IC1.8 (O), JP10.7
UART_RXD: D4.A, U3.P$15 (RXD)
UART_TXD: IC1.9 (I), U3.P$14 (TXD)
VBAT: C5.1, C6.1, C7.1, CN2.2, D1.C, D3.C, JP3.2, JP10.2, U2.3 (VBAT), U3.P$4 (VBAT@1), U3.P$5 (VBAT@2), U3.P$6 (VBAT@3)
VBUS: U3.P$25 (VBUS)
VCCIO: IC1.14 (VCC), JP10.4
VRTC: C9.1, U3.P$17 (VRTC)

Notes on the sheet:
STATUS LEDS
2.0K = 500mA
ANTENNA
10K = 100mA
POWER DECOUPLING
LEVEL SHIFTING
SIM CARD
1.0K = 1000mA
UART RI (Ring Indicator) State: Standby = High Voice Call = Goes low, call is established/caller hangs up goes high Data Call = Same as voice call SMS = Goes low, stays low 120ms, high URC = Goes low, stays low 120ms, URCs reported, high Making a Call = RI always stays high
LIPO CHARGER
AUDIO FILTERING
5.0K = 200mA
3.5MM HEADPHONE/MIC

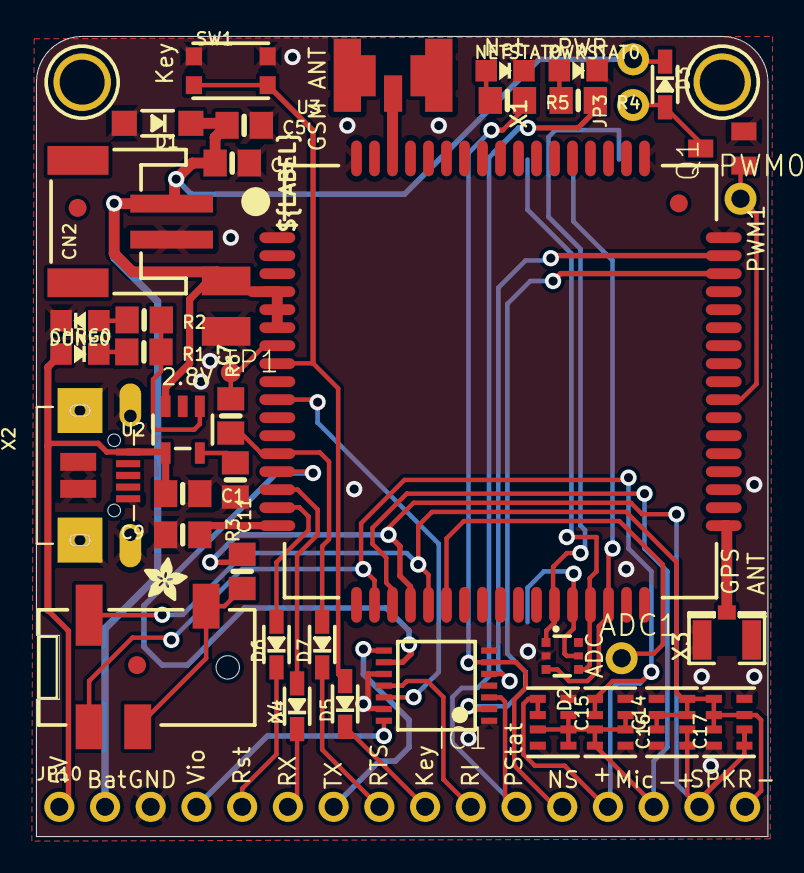
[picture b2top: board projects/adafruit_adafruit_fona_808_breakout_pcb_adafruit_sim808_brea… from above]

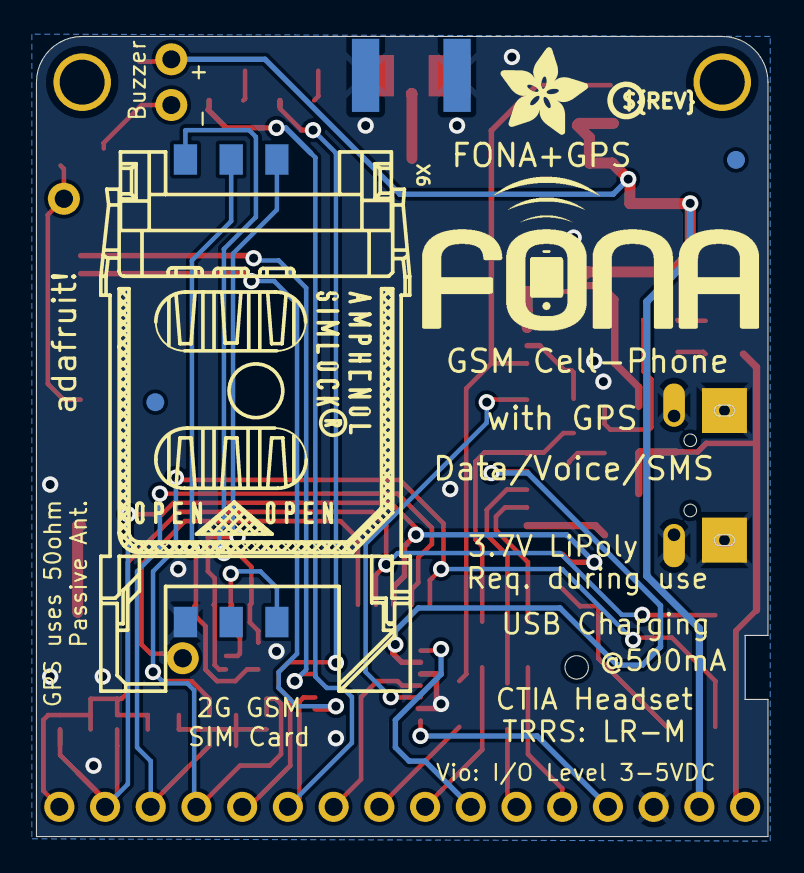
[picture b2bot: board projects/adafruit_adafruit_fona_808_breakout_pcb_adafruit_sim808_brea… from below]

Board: 2 copper layers, 40.6 x 44.5 mm, 54 parts (6 on the bottom side), 42 nets.

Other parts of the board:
U$21: ADAFRUIT_2.5MM
U$25: PCBFEAT-REV-040
U$26: FONA_LOGO
U$36: ADAFRUIT_5MM

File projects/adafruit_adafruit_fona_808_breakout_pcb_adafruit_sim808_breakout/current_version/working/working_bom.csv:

"Id";"Designator";"Footprint";"Quantity";"Designation";"Supplier and ref";
1;"JP10";"1X16_ROUND";1;"";;;
2;"U$33,U$34";"MOUNTINGHOLE_2.5_PLATED";2;"MOUNTINGHOLE2.5";;;
3;"D5,D6,D4,D3,D7";"SOD-323";5;"1N4148";;;
4;"X4";"4UCONN_18510";1;"4UCONN_18510";;;
5;"C14,C16";"RESPACK_4X0603";2;"33pF";;;
6;"R6";"0805-NO";1;"10K";;;
7;"C1";"0805-NO";1;"10µF";;;
8;"U2";"SOT23-5";1;"MCP73831T-2ACI/OT";;;
9;"FID3,FID1,FID2,FID5,FID4";"FIDUCIAL_1MM";5;"FIDUCIAL""";;;
10;"ADC1,PWM0";"1X01-CLEANBIG";2;"";;;
11;"C6";"0805-NO";1;"33pF";;;
12;"CHRG0";"CHIPLED_0805_NOOUTLINE";1;"ORANGE";;;
13;"PWRSTAT0";"CHIPLED_0805_NOOUTLINE";1;"BLUE";;;
14;"R2,R5,R4";"0805-NO";3;"1K";;;
15;"X1";"SMA_EDGELAUNCH_UFL";1;"uFL";;;
16;"C9,C11";"0805-NO";2;"10uF";;;
17;"C5";"0805-NO";1;"10pF";;;
18;"C17,C15";"RESPACK_4X0603";2;"10pF";;;
19;"U3";"SIM900_SMT";1;"SIM808";;;
20;"JP3";"1X02_ROUND";1;"BUZZ";;;
21;"R1";"0805-NO";1;"470";;;
22;"U$21";"ADAFRUIT_2.5MM";1;"";;;
23;"Q1";"SC59-BEC";1;"DTC143ZUAT106";;;
24;"D2";"SOT363";1;"SMF05C";;;
25;"DONE0";"CHIPLED_0805_NOOUTLINE";1;"GREEN";;;
26;"X2";"4UCONN_20329";1;"MicroB";;;
27;"R3";"0805-NO";1;"2K";;;
28;"NETSTAT0";"CHIPLED_0805_NOOUTLINE";1;"RED";;;
29;"C7";"C1210";1;"100uF";;;
30;"TP1";"TP11R";1;"TPTP11R";;;
31;"SW1";"BTN_KMR2_4.6X2.8";1;"KMR2";;;
32;"CN2";"JSTPH2";1;"JSTPH";;;
33;"IC1";"TSSOP14";1;"74VHCT125PW";;;
34;"X3";"U.FL";1;"uFL";;;
35;"D1";"SOD-123";1;"MMSZ5231BT1G";;;
36;"X6";"C707_10M006_512_2";1;"SIM_LOCKAMPHENOL";;;
37;"U$36";"ADAFRUIT_5MM";1;"";;;
38;"U$25";"PCBFEAT-REV-040";1;"";;;
39;"U$26";"FONA_LOGO";1;"";;;
